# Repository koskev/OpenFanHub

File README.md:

# OpenFanHub

This project aims to provide plug and play solution for controlling fans and reading temperatures

## Attention
 * The USB-Library is licensed under the SLA0044 License and therefore incompatible with the GPL. Until this is resolved the GPL does not apply to the "Firmware" folder.

## TODO
 * Finish PCB
   * Currently working on a barebone blue pill
   * Probably remove the option for two different µC options
 * Replace USB Lib
 * Implement Rust version as a learning experience?
   * But currently USB hates me :/
 * Replace the USB lib to be compatible with an open source license

## Features
 * Connection for 18 fans
    * 3 Fans form one group
    * 6 independently controllable
    * only one fan in each group reports rpm
    * 3 pin fans are supported but not regulated (I tried it, but ended but beeing to complicated since I plan on using 4 pin anyways)
 * 4 thermistor inputs
 * compatible with the corsair commander pro driver of the kernel
 * Compatible with the "blue pill" boards or an stm32f103c8tx in an LQFP48 package
    * The goal is to make is easy to solder and LQFP48 can be hard

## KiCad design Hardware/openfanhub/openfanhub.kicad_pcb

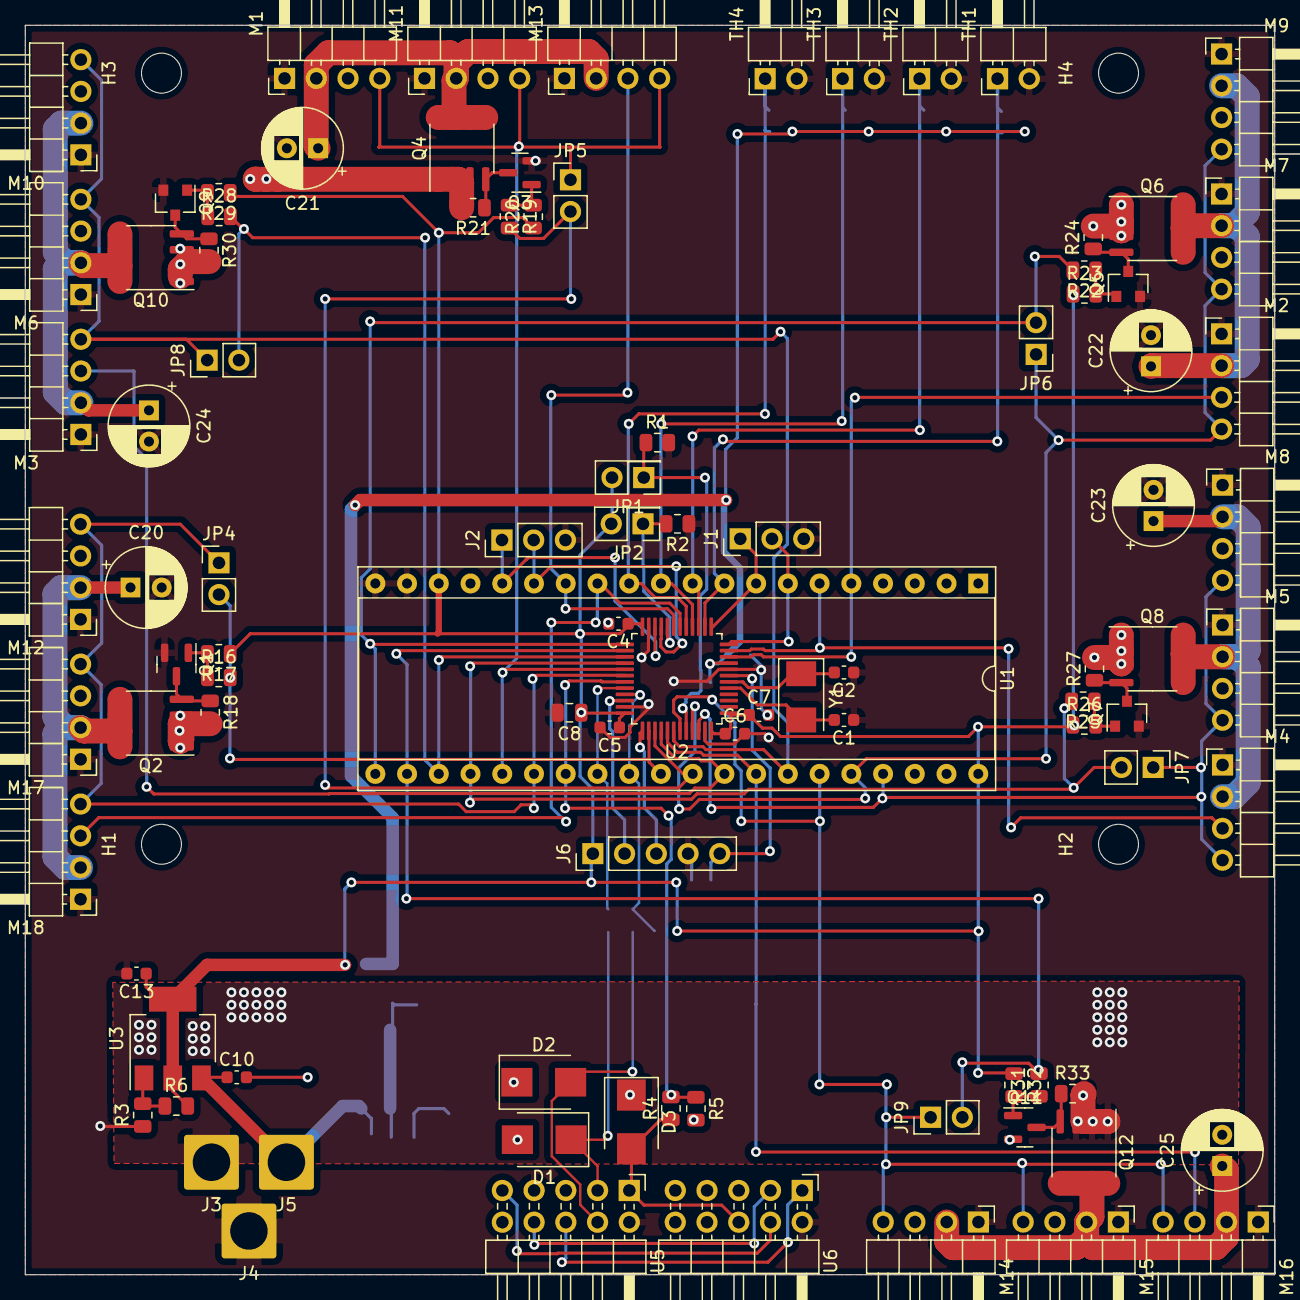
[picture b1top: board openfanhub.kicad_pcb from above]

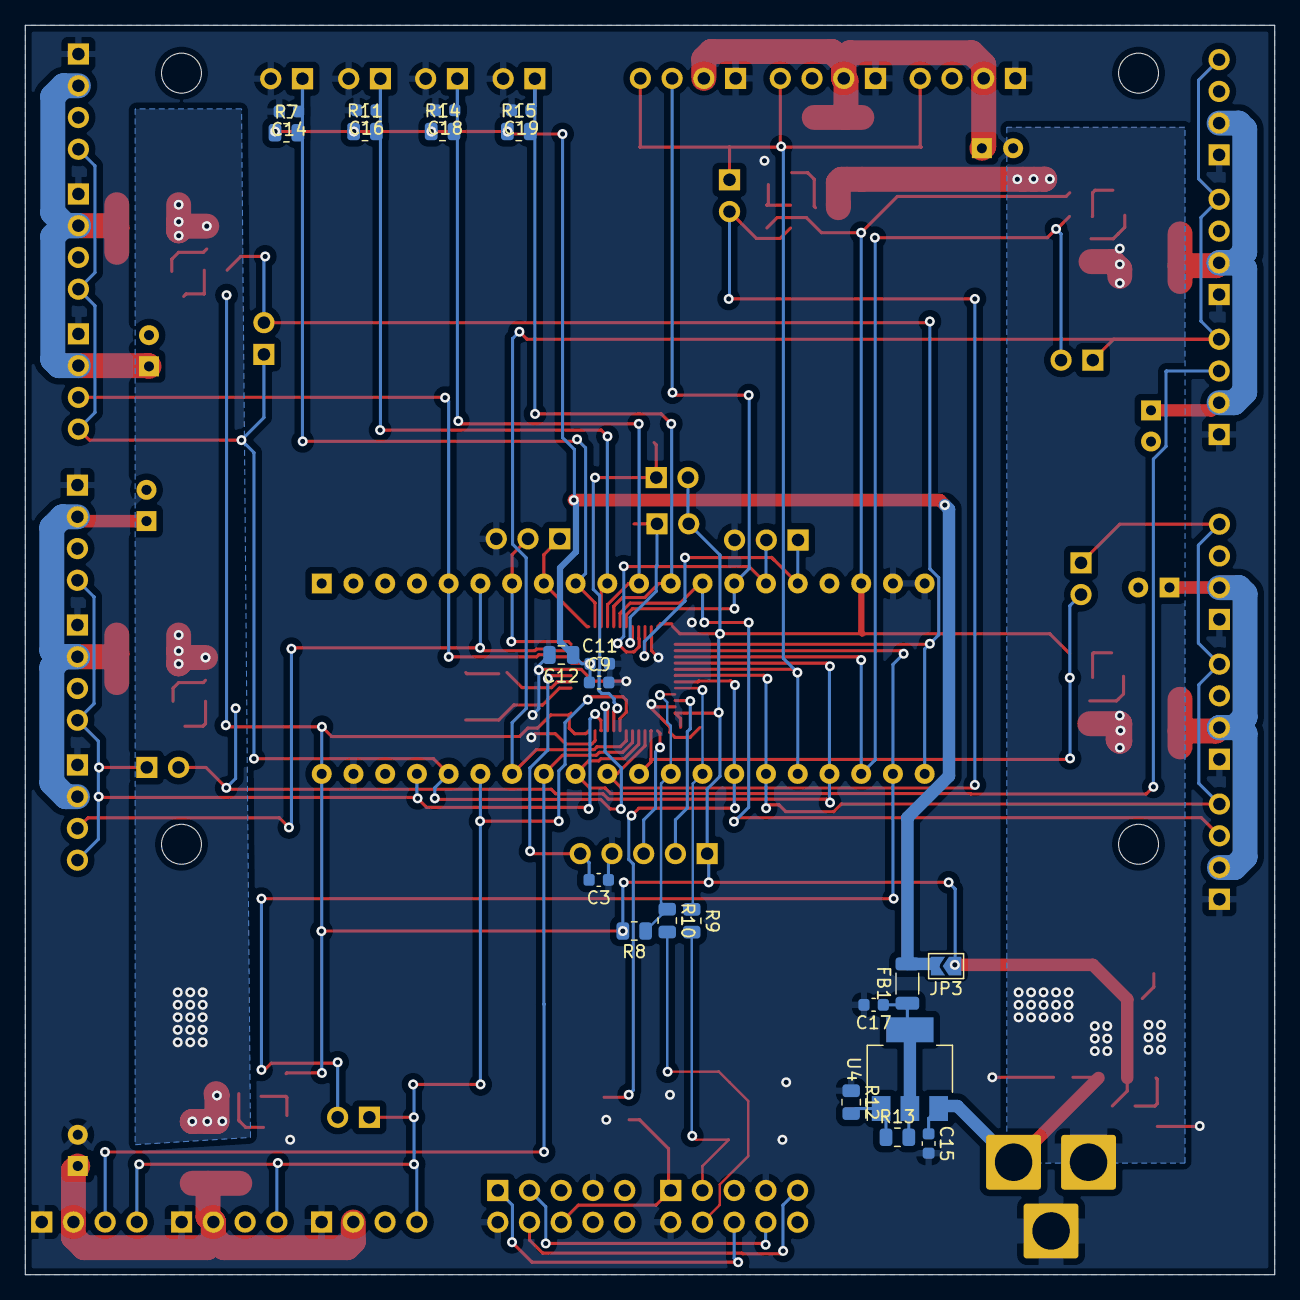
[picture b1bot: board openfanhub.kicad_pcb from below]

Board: 2 copper layers, 100.0 x 100.0 mm, 122 parts (22 on the bottom side), 68 nets.

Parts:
C1, C2: 22pF; C_0603_1608Metric
C3, C4, C5, C6, C7, C9: 100nF; C_0603_1608Metric
C8, C12: 10µF; C_0805_2012Metric
C10, C13, C14, C15, C16, C17, C18, C19: C; C_0603_1608Metric
C11: 10nF; C_0603_1608Metric
C20, C21, C22, C23, C24, C25: C_Polarized; CP_Radial_D6.3mm_P2.50mm
D1, D2, D3: D_TVS; D_SMB
FB1: FerriteBead; L_1206_3216Metric
H1, H2, H3, H4: MountingHole; MountingHole_3.2mm_M3
J1: UART; PinHeader_1x03_P2.54mm_Vertical
J2: I2C; PinHeader_1x03_P2.54mm_Vertical
J3: 12V in; SolderWire-2.5sqmm_1x01_D2.4mm_OD4.4mm
J4: GND in; SolderWire-2.5sqmm_1x01_D2.4mm_OD4.4mm
J5: 5V IN; SolderWire-2.5sqmm_1x01_D2.4mm_OD4.4mm
J6: SWD; PinHeader_1x05_P2.54mm_Vertical
JP1, JP2: Jumper_2_Open; PinHeader_2x01_P2.54mm_Vertical
JP3: 3.3V connect; SolderJumper-2_P1.3mm_Open_TrianglePad1.0x1.5mm
JP4, JP5, JP6, JP7, JP8, JP9: 3Pin Jumper; PinHeader_1x02_P2.54mm_Vertical
M1, M2, M3, M4, M5, M6, M7, M8, M9, M10, M11, M12, M13, M14, M15, M16, M17, M18: Fan_4pin; PinHeader_1x04_P2.54mm_Horizontal
Q1, Q3, Q5, Q7, Q9, Q11: Q_NMOS_GSD; SOT-23
Q2, Q4, Q6, Q8, Q10, Q12: AO449; SOIC-8_3.9x4.9mm_P1.27mm
R1, R2: 10k; R_0805_2012Metric
R3, R4, R5, R6, R7, R8, R9, R10, R11, R12, R13, R14, R15, R16, R17, R18, R19, R20, R21, R22, R23, R24, R25, R26, R27, R28, R29, R30, R31, R32, R33: R; R_0805_2012Metric
TH1, TH2, TH3, TH4: Thermistor; PinHeader_1x02_P2.54mm_Horizontal
U1: STM32F103C8T8_Board; DIP-40_W15.24mm_Socket
U2: STM32F103C8Tx; LQFP-48_7x7mm_P0.5mm
U3, U4: AMS1117; SOT-223
U5: USB_HEADER_IN; PinHeader_2x05_P2.54mm_Horizontal
U6: USB_HEADER_OUT; PinHeader_2x05_P2.54mm_Horizontal
Y1: Crystal; Crystal_SMD_5032-2Pin_5.0x3.2mm

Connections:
+3.3VA: C9.1, C11.1, C12.1, FB1.2, JP3.2 (B), R7.1, R11.1, R14.1, R15.1, U2.9 (VDDA)
+3V3: C4.1, C5.1, C6.1, C7.1, C8.1, C13.1, J6.1, JP1.2 (B), JP2.2 (B), JP3.1 (A), R6.2, R8.2, R17.1, R20.1, R23.1, R26.1, R29.1, R32.1, U1.18 (3.3V), U1.40 (3.3V), U2.1 (VBAT), U2.24 (VDD), U2.36 (VDD), U2.48 (VDD), U3.2 (Vout), U3.4 (Vout)
+5V: C10.1, C15.1, J5.1, U3.3 (Vin), U4.3 (Vin)
+12V: J3.1, Q2.1 (S), Q2.2 (S), Q2.3 (S), Q4.1 (S), Q4.2 (S), Q4.3 (S), Q6.1 (S), Q6.2 (S), Q6.3 (S), Q8.1 (S), Q8.2 (S), Q8.3 (S), Q10.1 (S), Q10.2 (S), Q10.3 (S), Q12.1 (S), Q12.2 (S), Q12.3 (S), R18.2, R21.2, R24.2, R27.2, R30.2, R33.2
/BOOT0: JP1.1 (A), R1.1, U2.44 (BOOT0)
/BOOT1: JP2.1 (A), R2.2, U2.20 (PB2)
/D1+: D2.2 (A2), R10.2, U5.4 (D2+)
/D1-: D1.1 (A1), R9.2, U5.3 (D1-)
/FAN1_PWM: JP6.1 (A), M2.4 (PWM), M7.4 (PWM), M9.4 (PWM), U1.36 (B8), U2.45 (PB8)
/FAN1_RPM: M2.3 (Tacho), U1.5 (A0), U2.10 (PA0)
/FAN1_SWITCH: JP6.2 (B), R22.2, U1.21 (B12), U2.25 (PB12)
/FAN2_PWM: JP7.1 (A), M4.4 (PWM), M5.4 (PWM), M8.4 (PWM), U1.37 (B9), U2.46 (PB9)
/FAN2_RPM: M4.3 (Tacho), U1.6 (A1), U2.11 (PA1)
/FAN2_SWITCH: JP7.2 (B), R25.2, U1.24 (B15), U2.28 (PB15)
/FAN3_PWM: JP8.1 (A), M3.4 (PWM), M6.4 (PWM), M10.4 (PWM), U1.34 (B6), U2.42 (PB6)
/FAN3_RPM: M3.3 (Tacho), U1.32 (B4), U2.40 (PB4)
/FAN3_SWITCH: JP8.2 (B), R28.2, U1.23 (B14), U2.27 (PB14)
/FAN4_PWM: JP9.1 (A), M14.4 (PWM), M15.4 (PWM), M16.4 (PWM), U1.35 (B7), U2.43 (PB7)
/FAN4_RPM: M16.3 (Tacho), U1.33 (B5), U2.41 (PB5)
/FAN4_SWITCH: JP9.2 (B), R31.2, U1.22 (B13), U2.26 (PB13)
/FAN5_PWM: JP4.1 (A), M12.4 (PWM), M17.4 (PWM), M18.4 (PWM), U1.26 (A9), U2.30 (PA9)
/FAN5_RPM: M18.3 (Tacho), U1.13 (B0), U2.18 (PB0)
/FAN5_SWITCH: JP4.2 (B), R16.2, U1.30 (A15), U2.38 (PA15)
/FAN6_PWM: JP5.1 (A), M1.4 (PWM), M11.4 (PWM), M13.4 (PWM), U1.25 (A8), U2.29 (PA8)
/FAN6_RPM: M13.3 (Tacho), U1.14 (B1), U2.19 (PB1)
/FAN6_SWITCH: JP5.2 (B), R19.2, U1.31 (B3), U2.39 (PB3)
/NRST: C3.2, J6.5, U2.7 (NRST)
/PWM_GROUPS/PWM_GROUP1/SWITCHED_POWER: C22.1, M2.2 (+), M7.2 (+), M9.2 (+), Q6.5 (D), Q6.6 (D), Q6.7 (D), Q6.8 (D)
/PWM_GROUPS/PWM_GROUP2/SWITCHED_POWER: C23.1, M4.2 (+), M5.2 (+), M8.2 (+), Q8.5 (D), Q8.6 (D), Q8.7 (D), Q8.8 (D)
/PWM_GROUPS/PWM_GROUP3/SWITCHED_POWER: C24.1, M3.2 (+), M6.2 (+), M10.2 (+), Q10.5 (D), Q10.6 (D), Q10.7 (D), Q10.8 (D)
/PWM_GROUPS/PWM_GROUP4/SWITCHED_POWER: C25.1, M14.2 (+), M15.2 (+), M16.2 (+), Q12.5 (D), Q12.6 (D), Q12.7 (D), Q12.8 (D)
/PWM_GROUPS/PWM_GROUP5/SWITCHED_POWER: C20.1, M12.2 (+), M17.2 (+), M18.2 (+), Q2.5 (D), Q2.6 (D), Q2.7 (D), Q2.8 (D)
/PWM_GROUPS/PWM_GROUP6/SWITCHED_POWER: C21.1, M1.2 (+), M11.2 (+), M13.2 (+), Q4.5 (D), Q4.6 (D), Q4.7 (D), Q4.8 (D)
/SCL: J2.2, U1.15 (B10), U2.21 (PB10)
/SDA: J2.1, U1.16 (B11), U2.22 (PB11)
/SWD_CLK: J6.3, U2.37 (PA14)
/SWD_IO: J6.2, U2.34 (PA13)
/TEMP1_IN: C14.1, R7.2, TH1.1, U1.9 (A4), U2.14 (PA4)
/TEMP2_IN: C16.1, R11.2, TH2.1, U1.10 (A5), U2.15 (PA5)
/TEMP3_IN: C18.1, R14.2, TH3.1, U1.11 (A6), U2.16 (PA6)
/TEMP4_IN: C19.1, R15.2, TH4.1, U1.12 (A7), U2.17 (PA7)
/UART_RX: J1.1, U1.8 (A3), U2.13 (PA3)
/UART_TX: J1.2, U1.7 (A2), U2.12 (PA2)
/USB_D+: R8.1, R10.1, U1.29 (A12), U2.33 (PA12)
/USB_D-: R9.1, U1.28 (A11), U2.32 (PA11)
/VBUS: D3.2 (A2), R4.1, U5.1 (5V), U6.6 (5V)
/VBUS_SENSE: R4.2, R5.1, U1.27 (A10), U2.31 (PA10)
GND: C1.1, C2.1, C3.1, C4.2, C5.2, C6.2, C7.2, C8.2, C9.2, C10.2, C11.2, C12.2, C13.2, C14.2, C15.2, C16.2, C17.2, C18.2, C19.2, C20.2, C21.2, C22.2, C23.2, C24.2, C25.2, D1.2 (A2), D2.1 (A1), D3.1 (A1), J1.3, J2.3, J4.1, J6.4, M1.1 (-), M2.1 (-), M3.1 (-), M4.1 (-), M5.1 (-), M6.1 (-), M7.1 (-), M8.1 (-), M9.1 (-), M10.1 (-), M11.1 (-), M12.1 (-), M13.1 (-), M14.1 (-), M15.1 (-), M16.1 (-), M17.1 (-), M18.1 (-), Q1.2 (S), Q3.2 (S), Q5.2 (S), Q7.2 (S), Q9.2 (S), Q11.2 (S), R1.2, R2.1, R3.1, R5.2, R12.1, TH1.2, TH2.2, TH3.2, TH4.2, U1.19 (GND), U1.20 (GND), U1.39 (GND), U2.8 (VSSA), U2.23 (VSS), U2.35 (VSS), U2.47 (VSS), U5.2 (GND), U5.7 (GND), U6.2 (GND), U6.7 (GND)
unnamed: C1.2, U2.5 (PD0), Y1.2
unnamed: C2.2, U2.6 (PD1), Y1.1
unnamed: C17.1, FB1.1, R13.2, U4.2 (Vout), U4.4 (Vout)
unnamed: Q1.1 (G), R16.1, R17.2
unnamed: Q1.3 (D), Q2.4 (G), R18.1
unnamed: Q3.1 (G), R19.1, R20.2
unnamed: Q3.3 (D), Q4.4 (G), R21.1
unnamed: Q5.1 (G), R22.1, R23.2
unnamed: Q5.3 (D), Q6.4 (G), R24.1
unnamed: Q7.1 (G), R25.1, R26.2
unnamed: Q7.3 (D), Q8.4 (G), R27.1
unnamed: Q9.1 (G), R28.1, R29.2
unnamed: Q9.3 (D), Q10.4 (G), R30.1
unnamed: Q11.1 (G), R31.1, R32.2
unnamed: Q11.3 (D), Q12.4 (G), R33.1
unnamed: R3.2, R6.1, U3.1 (ADJ)
unnamed: R12.2, R13.1, U4.1 (ADJ)
unnamed: U5.6 (5V), U6.1 (5V)
unnamed: U5.8 (D2-), U6.3 (D1-)
unnamed: U5.9 (D2+), U6.4 (D2+)

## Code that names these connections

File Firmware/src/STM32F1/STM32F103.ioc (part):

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Mcu.Name=STM32F103C(8-B)Tx
Mcu.Package=LQFP48
Mcu.UserName=STM32F103C8Tx
PA0-WKUP.GPIOParameters=GPIO_PuPd
PA0-WKUP.GPIO_PuPd=GPIO_PULLUP
PA0-WKUP.Signal=S_TIM2_CH1_ETR
PA1.GPIOParameters=GPIO_PuPd
PA1.GPIO_PuPd=GPIO_PULLUP
PA1.Signal=S_TIM2_CH2
PA10.Signal=S_TIM1_CH3
PA11.Mode=Device
PA11.Signal=USB_DM
PA12.Mode=Device
PA12.Signal=USB_DP
PA13.Mode=Serial_Wire
PA13.Signal=SYS_JTMS-SWDIO
PA14.Mode=Serial_Wire
PA14.Signal=SYS_JTCK-SWCLK
PA15.GPIOParameters=GPIO_PuPd,GPIO_Label
PA15.GPIO_Label=FAN5_SWITCH
PA15.GPIO_PuPd=GPIO_NOPULL
PA15.Signal=GPIO_Output
PA2.Mode=Asynchronous
PA2.Signal=USART2_TX
PA3.Mode=Asynchronous
PA3.Signal=USART2_RX
PA4.Signal=ADCx_IN4
PA5.Signal=ADCx_IN5
PA6.Signal=ADCx_IN6
PA7.Signal=ADCx_IN7
PA8.Signal=S_TIM1_CH1
PA9.Signal=S_TIM1_CH2
PB0.GPIOParameters=GPIO_PuPd
PB0.GPIO_PuPd=GPIO_PULLUP
PB0.Signal=S_TIM3_CH3
PB1.GPIOParameters=GPIO_PuPd
PB1.GPIO_PuPd=GPIO_PULLUP
PB1.Signal=S_TIM3_CH4
PB10.Mode=I2C
PB10.Signal=I2C2_SCL
PB11.Mode=I2C
PB11.Signal=I2C2_SDA
PB12.GPIOParameters=GPIO_PuPd,GPIO_Label
PB12.GPIO_Label=FAN1_SWITCH
PB12.GPIO_PuPd=GPIO_NOPULL
PB12.Signal=GPIO_Output
PB13.GPIOParameters=GPIO_PuPd,GPIO_Label
PB13.GPIO_Label=FAN2_SWITCH
PB13.GPIO_PuPd=GPIO_NOPULL
PB13.Signal=GPIO_Output
PB14.GPIOParameters=GPIO_PuPd,GPIO_Label
PB14.GPIO_Label=FAN3_SWITCH
PB14.GPIO_PuPd=GPIO_NOPULL
PB14.Signal=GPIO_Output
PB15.GPIOParameters=GPIO_PuPd,GPIO_Label
PB15.GPIO_Label=FAN4_SWITCH
PB15.GPIO_PuPd=GPIO_NOPULL
PB15.Signal=GPIO_Output
PB3.GPIOParameters=GPIO_PuPd,GPIO_Label
PB3.GPIO_Label=FAN6_SWITCH
PB3.GPIO_PuPd=GPIO_NOPULL
PB3.Signal=GPIO_Output
PB4.GPIOParameters=GPIO_PuPd
PB4.GPIO_PuPd=GPIO_PULLUP
PB4.Signal=S_TIM3_CH1
PB5.GPIOParameters=GPIO_PuPd
PB5.GPIO_PuPd=GPIO_PULLUP
PB5.Signal=S_TIM3_CH2
PB6.Signal=S_TIM4_CH1
PB7.Signal=S_TIM4_CH2
PB8.Signal=S_TIM4_CH3
PB9.Signal=S_TIM4_CH4
PC14-OSC32_IN.Mode=LSE-External-Oscillator
PC14-OSC32_IN.Signal=RCC_OSC32_IN
PC15-OSC32_OUT.Mode=LSE-External-Oscillator
PC15-OSC32_OUT.Signal=RCC_OSC32_OUT
PD0-OSC_IN.Mode=HSE-External-Oscillator
PD0-OSC_IN.Signal=RCC_OSC_IN
PD1-OSC_OUT.Mode=HSE-External-Oscillator
PD1-OSC_OUT.Signal=RCC_OSC_OUT
RCC.SYSCLKFreq_VALUE=72000000
RCC.SYSCLKSource=RCC_SYSCLKSOURCE_PLLCLK
board=custom

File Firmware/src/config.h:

#define TIMER1_HANDLE &htim1
#define TIMER2_HANDLE &htim2
#define TIMER3_HANDLE &htim3
#define TIMER4_HANDLE &htim4

#define FAN1_PWM_TIMER TIMER1_HANDLE
#define FAN1_PWM_CHANNEL TIM_CHANNEL_1
#define FAN1_PWM_PORT GPIOA
#define FAN1_PWM_PIN GPIO_PIN_8
#define FAN1_IC_TIMER TIMER2_HANDLE
#define FAN1_IC_CHANNEL TIM_CHANNEL_1
#define FAN1_IC_CHANNEL_ACTIVE HAL_TIM_ACTIVE_CHANNEL_1
#define FAN1_POWER_SWITCH_PORT GPIOB
#define FAN1_POWER_SWITCH_PIN GPIO_PIN_12

#define FAN2_PWM_TIMER TIMER1_HANDLE
#define FAN2_PWM_CHANNEL TIM_CHANNEL_2
#define FAN2_PWM_PORT GPIOA
#define FAN2_PWM_PIN GPIO_PIN_9
#define FAN2_IC_TIMER TIMER2_HANDLE
#define FAN2_IC_CHANNEL TIM_CHANNEL_2
#define FAN2_IC_CHANNEL_ACTIVE HAL_TIM_ACTIVE_CHANNEL_2
#define FAN2_POWER_SWITCH_PORT GPIOB
#define FAN2_POWER_SWITCH_PIN GPIO_PIN_13

#define FAN3_PWM_TIMER TIMER4_HANDLE
#define FAN3_PWM_CHANNEL TIM_CHANNEL_1
#define FAN3_PWM_PORT GPIOB
#define FAN3_PWM_PIN GPIO_PIN_6
#define FAN3_IC_TIMER TIMER3_HANDLE
#define FAN3_IC_CHANNEL TIM_CHANNEL_1
#define FAN3_IC_CHANNEL_ACTIVE HAL_TIM_ACTIVE_CHANNEL_1
#define FAN3_POWER_SWITCH_PORT GPIOB
#define FAN3_POWER_SWITCH_PIN GPIO_PIN_14

#define FAN4_PWM_TIMER TIMER4_HANDLE
#define FAN4_PWM_CHANNEL TIM_CHANNEL_2
#define FAN4_PWM_PORT GPIOB
#define FAN4_PWM_PIN GPIO_PIN_7
#define FAN4_IC_TIMER TIMER3_HANDLE
#define FAN4_IC_CHANNEL TIM_CHANNEL_2
#define FAN4_IC_CHANNEL_ACTIVE HAL_TIM_ACTIVE_CHANNEL_2
#define FAN4_POWER_SWITCH_PORT GPIOB
#define FAN4_POWER_SWITCH_PIN GPIO_PIN_15

#define FAN5_PWM_TIMER TIMER4_HANDLE
#define FAN5_PWM_CHANNEL TIM_CHANNEL_3
#define FAN5_PWM_PORT GPIOB
#define FAN5_PWM_PIN GPIO_PIN_8
#define FAN5_IC_TIMER TIMER3_HANDLE
#define FAN5_IC_CHANNEL TIM_CHANNEL_3
#define FAN5_IC_CHANNEL_ACTIVE HAL_TIM_ACTIVE_CHANNEL_3
#define FAN5_POWER_SWITCH_PORT GPIOA
#define FAN5_POWER_SWITCH_PIN GPIO_PIN_15

#define FAN6_PWM_TIMER TIMER4_HANDLE
#define FAN6_PWM_CHANNEL TIM_CHANNEL_4
#define FAN6_PWM_PORT GPIOB
#define FAN6_PWM_PIN GPIO_PIN_9
#define FAN6_IC_TIMER TIMER3_HANDLE
#define FAN6_IC_CHANNEL TIM_CHANNEL_4
#define FAN6_IC_CHANNEL_ACTIVE HAL_TIM_ACTIVE_CHANNEL_4
#define FAN6_POWER_SWITCH_PORT GPIOB
#define FAN6_POWER_SWITCH_PIN GPIO_PIN_3

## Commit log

2021-12-26 Non crashing version
2021-12-26 Prepare USB rx
2021-12-26 Sending data working
2021-12-26 Enable on rx callback
2021-12-26 First working version with all sensors to 0
2021-12-26 Fix wrong descriptor. Still problems with sending data back
2021-12-26 Fix problems with corrupted data
2021-12-27 Add temperature output
2021-12-27 Fix descriptor
2021-12-27 Fix report size
2021-12-27 Fix endpoint sizes. Greatly improves speed
2021-12-27 Reduce bInterval to 1 to improve performance even more
2021-12-27 Fix bInterval and descriptor size in CubeMX
2021-12-27 Add timer etc
2021-12-27 Rearrange timers
2021-12-27 Add support for rpm reading
2021-12-28 Update pin feature usage Enable adc, i2c, uart etc.
2021-12-28 Add detection of 4 pin fans. Add config file.
2021-12-28 Update schematics with new pin layout
2021-12-28 Fix alignment
2021-12-28 Update timers
2021-12-28 Add missing sources in cmake
2021-12-28 More error prevention
2021-12-28 Use pullups for rpm inputs
2021-12-28 Fix fan init
2021-12-28 Fix timer prescaler and period
2021-12-28 Idea to enable 3 pin PWM support with minimal components
2021-12-28 Fix switch to deactivate fan
2021-12-28 Enable fan by default (even if µC is offline)
2021-12-28 Add support for turning fans off
2021-12-28 Set rpm to zero after some overflows
2021-12-29 Update files to kicad 6
2021-12-29 Add support for 4 temp probes. They are constantly read using dma
2021-12-29 Copy init code to openfanhub as cubemx messes up the dma adc init order
2021-12-29 Move fan code to a separate file
2021-12-29 Add missing files
2021-12-29 Move more functions in fan file
2021-12-29 Minor cleanup
2021-12-30 Add v6 schematic
2021-12-31 Add first (badly) routed version. Still need to polish it and check all power/signal paths
2022-01-09 First pcb version
2022-01-16 Update PCB. Move Power and USB to the same side
2022-01-16 Make PCB smaller
2022-01-16 Update silkscreen
2022-01-18 Update (not sure what)
2023-07-25 Old hid
2023-08-06 Save work. Working usb hid
2023-08-06 add misc files
2024-02-13 Debug
2024-02-13 Add readme
2024-02-13 Add license
2024-02-22 Add all dependencies for firmware in repo
2024-02-22 Add TODOs to readme and disclaimer about the license
